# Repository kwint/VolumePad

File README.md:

# VolumePad

Proof of concept of a numpad / macropad with motorized faders to control volume. Fader position is also updated if you change the volume on the pc.

The main problem it tries to solve is noisy friends in discord while you are trying to clutch a csgo match

Current state of the project; PCB needs a lot of work, the original motor driver uses to much power and the fingerprint of the faders is wrong. The microcontoller code fully works, it uses MIDI for communication with the host. On windows you can use [MIDI Mixer](https://www.midi-mixer.com/). Haven't found a similar solution yet on linux, but shouldn't be hard to make. (The code in `code/host` is from before I moved the project over to MIDI).

https://user-images.githubusercontent.com/7907280/210675597-fe70f985-09b6-4afa-9840-3089a5ae9c90.mp4

## TODO:
### Code:
 - Create code for host machine
 - The capacitive button check needs work, might be electrical related
 - Clean up

### Electrical
 - Use newer motor driver
 - Fix footprint of faders
 - I think something is wrong with the capacitive button wiring

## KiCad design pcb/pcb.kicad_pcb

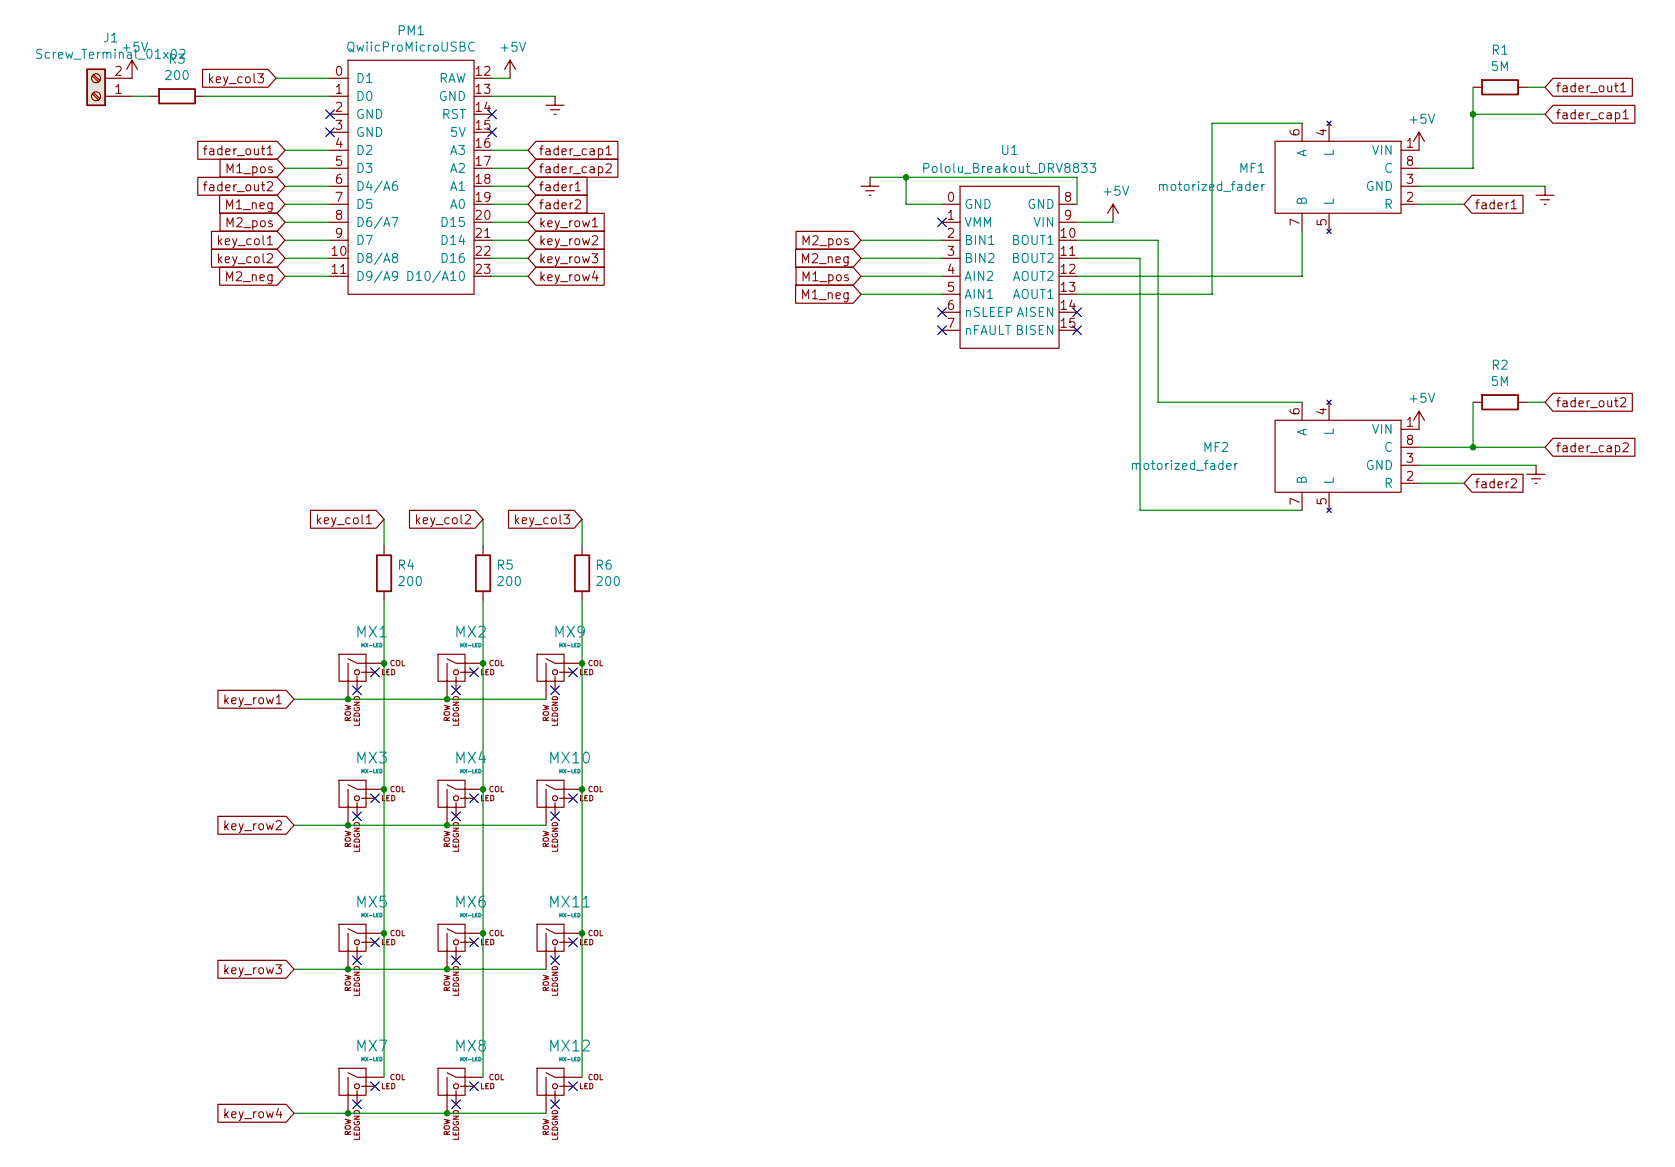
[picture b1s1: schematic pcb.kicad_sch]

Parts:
J1: Screw_Terminal_01x02; TerminalBlock_bornier-2_P5.08mm
MF1, MF2: motorized_fader
MX1, MX2, MX3, MX4, MX5, MX6, MX7, MX8, MX9, MX10, MX11, MX12: MX-LED; SW_Cherry_MX_1.00u_PCB
PM1: QwiicProMicroUSBC
R1, R2: 5M; R_Axial_DIN0207_L6.3mm_D2.5mm_P10.16mm_Horizontal
R3, R4, R5, R6: 200; R_Axial_DIN0207_L6.3mm_D2.5mm_P10.16mm_Horizontal
U1: Pololu_Breakout_DRV8833; Pololu_DRV8833

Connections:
+5V: J1.2, MF1.1 (VIN), MF2.1 (VIN), PM1.12 (RAW), U1.9 (VIN)
Earth: MF1.3 (GND), MF2.3 (GND), PM1.13 (GND), U1.0 (GND), U1.8 (GND)
M1_neg: PM1.7 (D5), U1.5 (AIN1)
M1_pos: PM1.5 (D3), U1.4 (AIN2)
M2_neg: PM1.11 (D9/A9), U1.3 (BIN2)
M2_pos: PM1.8 (D6/A7), U1.2 (BIN1)
unnamed: J1.1, R3.2
unnamed: MF1.6 (A), U1.13 (AOUT1)
unnamed: MF1.7 (B), U1.12 (AOUT2)
unnamed: MF2.6 (A), U1.10 (BOUT1)
unnamed: MF2.7 (B), U1.11 (BOUT2)
unnamed: MX1.1 (COL), MX3.1 (COL), MX5.1 (COL), MX7.1 (COL), R4.2
unnamed: MX2.1 (COL), MX4.1 (COL), MX6.1 (COL), MX8.1 (COL), R5.2
unnamed: MX9.1 (COL), MX10.1 (COL), MX11.1 (COL), MX12.1 (COL), R6.2
unnamed: PM1.1 (D0), R3.1
fader1: MF1.2 (R), PM1.18 (A1)
fader2: MF2.2 (R), PM1.19 (A0)
fader_cap1: MF1.8 (C), PM1.16 (A3), R1.2
fader_cap2: MF2.8 (C), PM1.17 (A2), R2.2
fader_out1: PM1.4 (D2), R1.1
fader_out2: PM1.6 (D4/A6), R2.1
key_col1: PM1.9 (D7), R4.1
key_col2: PM1.10 (D8/A8), R5.1
key_col3: PM1.0 (D1), R6.1
key_row1: MX1.2 (ROW), MX2.2 (ROW), MX9.2 (ROW), PM1.20 (D15)
key_row2: MX3.2 (ROW), MX4.2 (ROW), MX10.2 (ROW), PM1.21 (D14)
key_row3: MX5.2 (ROW), MX6.2 (ROW), MX11.2 (ROW), PM1.22 (D16)
key_row4: MX7.2 (ROW), MX8.2 (ROW), MX12.2 (ROW), PM1.23 (D10/A10)

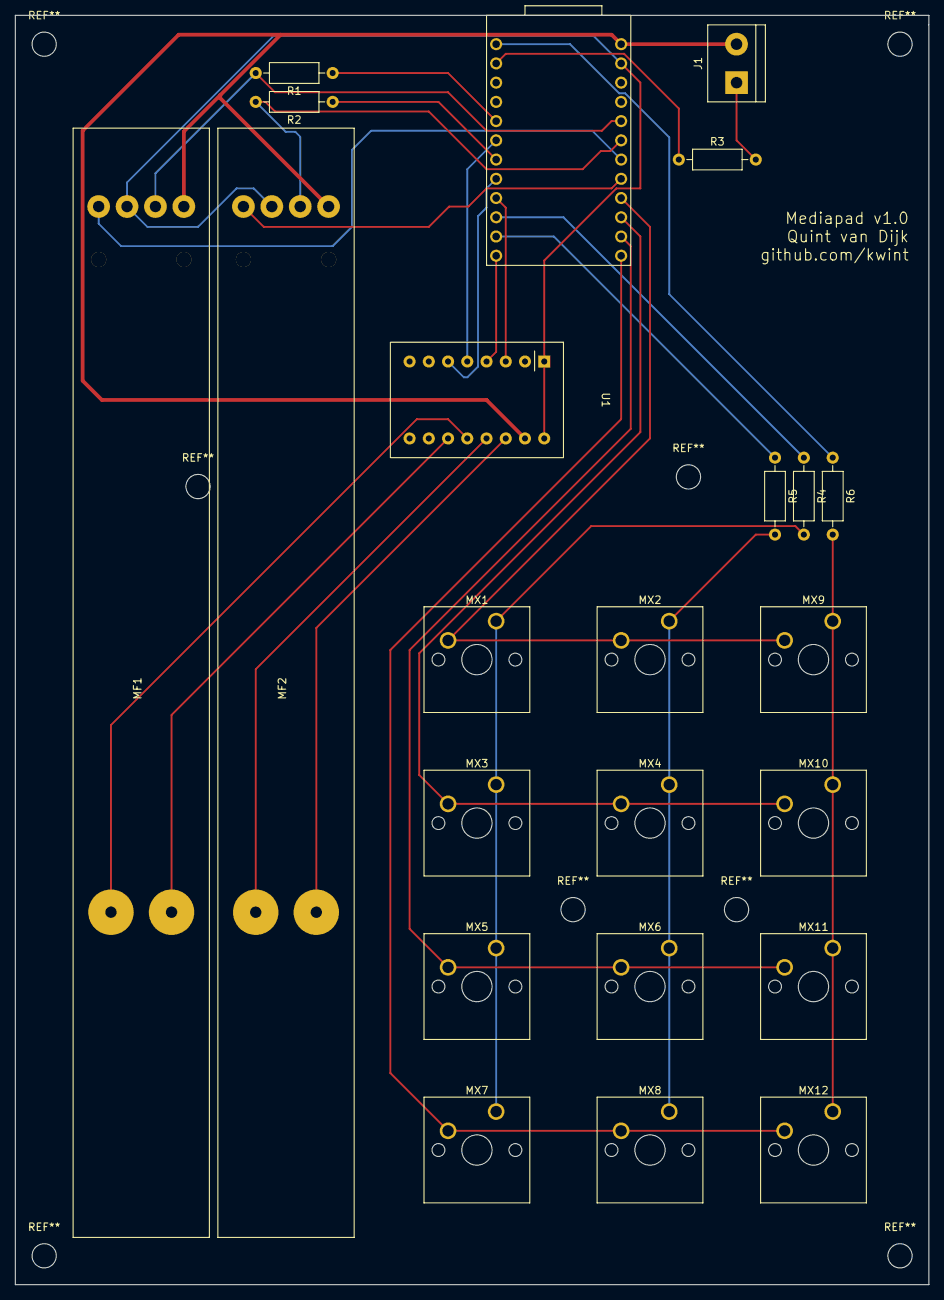
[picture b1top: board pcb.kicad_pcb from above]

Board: 2 copper layers, 120.6 x 167.6 mm, 23 parts (0 on the bottom side), 28 nets.

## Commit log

2023-01-04 init commit
2023-01-04 Structred code and removing robust_serial
2023-01-05 Arduino code cleanup
2023-01-05 spelling
2023-01-05 Added video
2023-03-12 WIP async and new pcb layout
2023-11-24 move to midi
2023-11-24 wip async
2024-02-04 Allow for feedback
2024-12-28 Don't move slider when touched, updated readme
